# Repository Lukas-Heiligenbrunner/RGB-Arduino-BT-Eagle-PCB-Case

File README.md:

# RGB colorchanger via Bluetooth - Arduino Sketch, case, eagle print

### Here you can get:

* A eagle print
* A appropriate openscad case
* The Arduino sketch

The Android app is in a seperate Repo! <a href="https://github.com/Lukas-Heiligenbrunner/RGB-Arduino-BT-App">HERE</a>

## wiring:

## Download links

### v1.1

<a href="https://github.com/Lukas-Heiligenbrunner/RGB-Arduino-BT-Eagle-PCB-Case/archive/v1.1.zip">Download</a>

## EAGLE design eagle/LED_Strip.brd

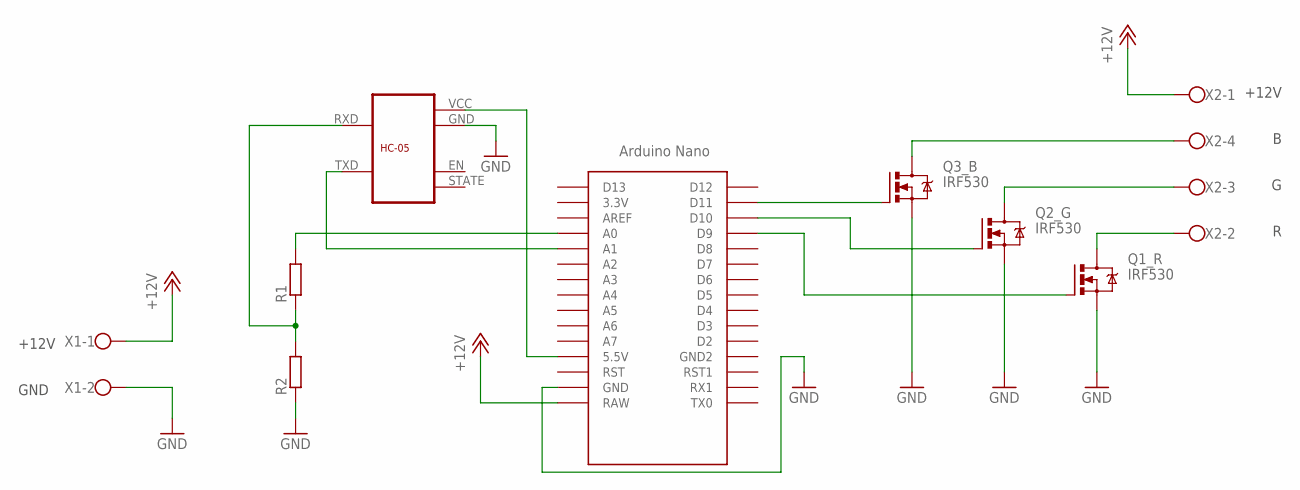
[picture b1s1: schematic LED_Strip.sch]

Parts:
Q1_R, Q2_G, Q3_B: IRF530; TO220BV
R1, R2: R-EU0207/10; 0207/10
U$1: PAC_BLUETOOTH_HC-05; BLUETOOTH_HC-05
U$2: NANO
X1: W237-102_L
X2: W237-04P_R; W237-4P_R

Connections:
+12V: U$2.RAW, X1.1, X2.1
GND: Q1_R.S, Q2_G.S, Q3_B.S, R2.1, U$1.GND, U$2.GND, X1.2
unnamed: Q1_R.D, X2.2
unnamed: Q3_B.G, U$2.D11
unnamed: Q2_G.G, U$2.D10
unnamed: Q1_R.G, U$2.D9
unnamed: Q2_G.D, X2.3
unnamed: Q3_B.D, X2.4
unnamed: U$1.VCC, U$2.5V (5.5V)
unnamed: R1.1, R2.2, U$1.RXD
unnamed: R1.2, U$2.A0
unnamed: U$1.TXD, U$2.A1

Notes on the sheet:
+12V
GND

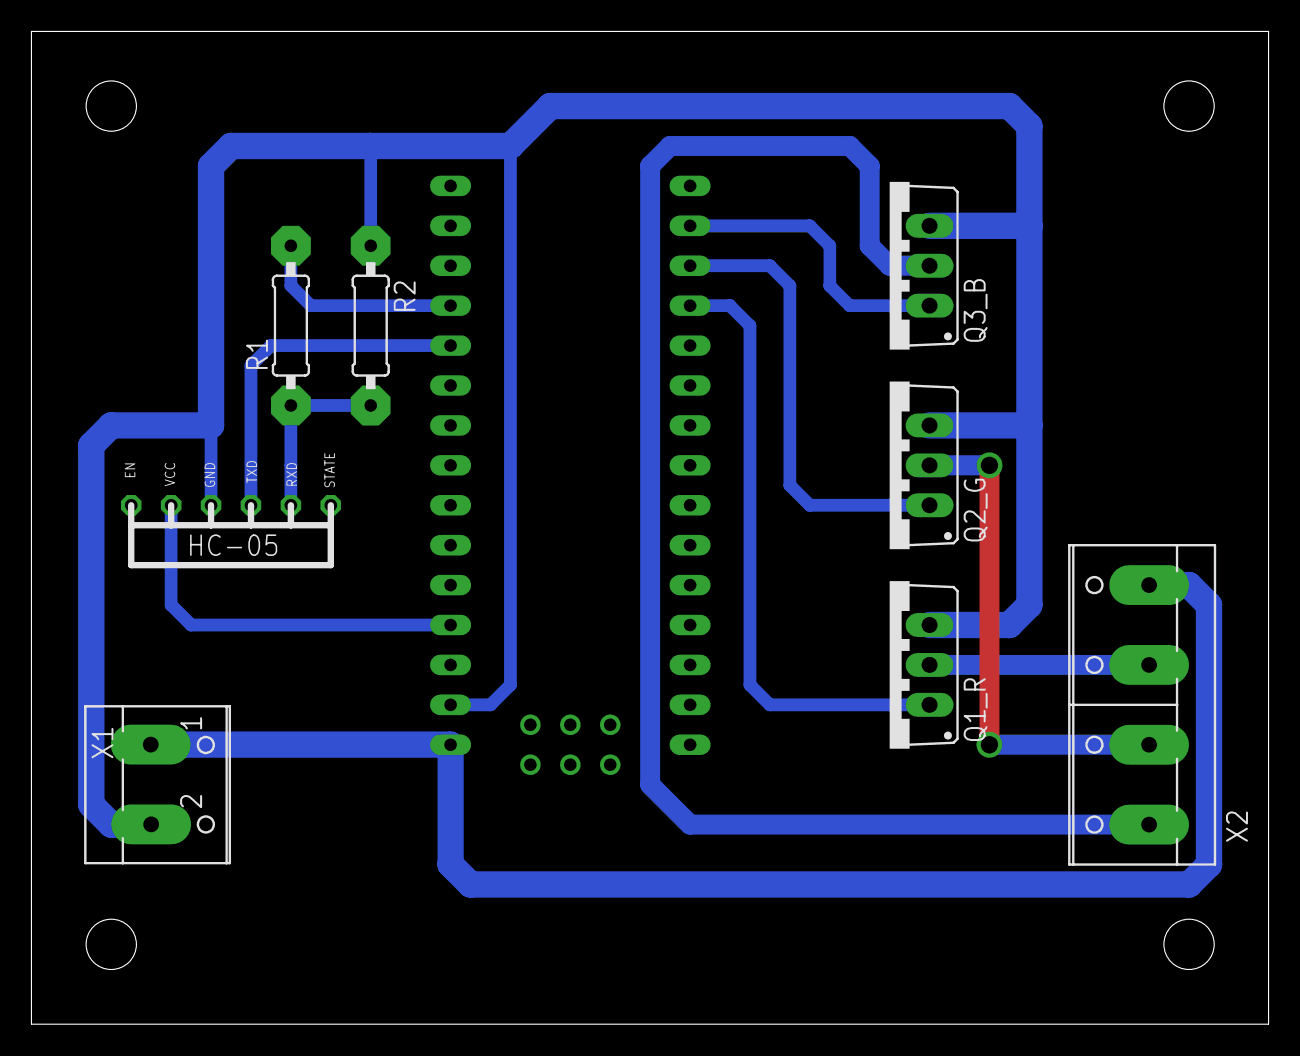
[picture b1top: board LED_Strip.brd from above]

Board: 2 copper layers, 78.7 x 63.2 mm, 9 parts (0 on the bottom side), 12 nets.

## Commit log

2018-05-10 added new files
2018-05-10 edited readme...
2018-05-10 added arduino sketch
2019-01-24 used code form @TaviTav
2019-01-24 added Frizing sketch by @TaviTav
2019-01-24 added fritzing schematic
